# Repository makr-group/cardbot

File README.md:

╔══════════════════════════════════════════════════════════════════╗
    ║                                                                  ║
    ║     ██████╗ █████╗ ██████╗ ██████╗ ██████╗  ██████╗ ████████╗    ║
    ║    ██╔════╝██╔══██╗██╔══██╗██╔══██╗██╔══██╗██╔═══██╗╚══██╔══╝    ║
    ║    ██║     ███████║██████╔╝██║  ██║██████╔╝██║   ██║   ██║       ║
    ║    ██║     ██╔══██║██╔══██╗██║  ██║██╔══██╗██║   ██║   ██║       ║
    ║    ╚██████╗██║  ██║██║  ██║██████╔╝██████╔╝╚██████╔╝   ██║       ║
    ║     ╚═════╝╚═╝  ╚═╝╚═╝  ╚═╝╚═════╝ ╚═════╝  ╚═════╝    ╚═╝       ║
    ║                                                                  ║
    ╚══════════════════════════════════════════════════════════════════╝
    
      █▄▄ █▄█   █▀▄▀█ ▄▀█ █▄▀ █▀█
      █▄█ ░█░   █░▀░█ █▀█ █░█ █▀▄

**Cardbot** is a open source robotics project desinged to bring low costs entry level robots
to students and kids. This project was started by the non-profit Makr Group (aka Makr) to
bring robotics to under served communities in Omaha, Nebraska, USA. With the goal to
kickstart intrest in technology and robotics. The Project is ongoing and slowly growing with 
the capbilites of the robots.

Cardbot is shared under the **Creative Commons Attribution-ShareAlike 4.0 International** license.

## Current Features

- Controller driven Bots with a programmable autonomus mode
- Phone Driven Bots (Broken)
- 3D printer files
- Laser cutter files
- Build Instuctions

## Planned Features

- Full programming instuctions
- Class lesson plans
- Alternative Build Lists

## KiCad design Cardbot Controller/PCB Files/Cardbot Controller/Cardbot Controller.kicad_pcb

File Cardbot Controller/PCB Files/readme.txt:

Files for Controller PCB both Gerber and KiCad.

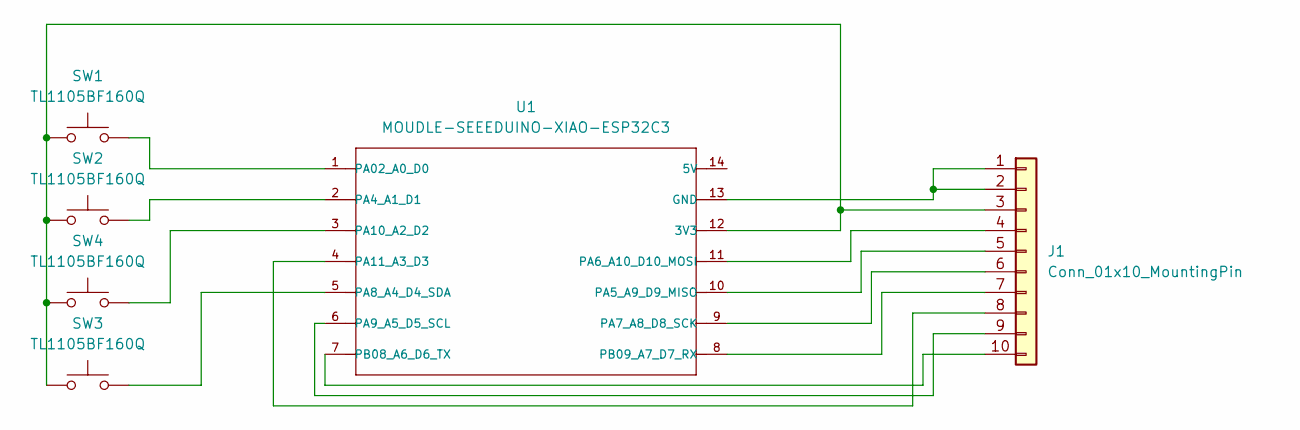
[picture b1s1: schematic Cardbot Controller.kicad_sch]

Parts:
J1: Conn_01x10_MountingPin
SW1, SW2, SW3, SW4: TL1105BF160Q
U1: MOUDLE-SEEEDUINO-XIAO-ESP32C3; MOUDLE14P-SMD-2.54-21X17.8MM

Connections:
unnamed: J1.1, J1.2, U1.13 (GND)
unnamed: J1.3, SW1.1, SW2.1, SW3.1, SW4.1, U1.12 (3V3)
unnamed: J1.4, U1.11 (PA6_A10_D10_MOSI)
unnamed: J1.5, U1.10 (PA5_A9_D9_MISO)
unnamed: J1.6, U1.9 (PA7_A8_D8_SCK)
unnamed: J1.7, U1.8 (PB09_A7_D7_RX)
unnamed: J1.8, U1.4 (PA11_A3_D3)
unnamed: J1.9, U1.6 (PA9_A5_D5_SCL)
unnamed: J1.10, U1.7 (PB08_A6_D6_TX)
unnamed: SW1.2, U1.1 (PA02_A0_D0)
unnamed: SW2.2, U1.2 (PA4_A1_D1)
unnamed: SW3.2, U1.5 (PA8_A4_D4_SDA)
unnamed: SW4.2, U1.3 (PA10_A2_D2)

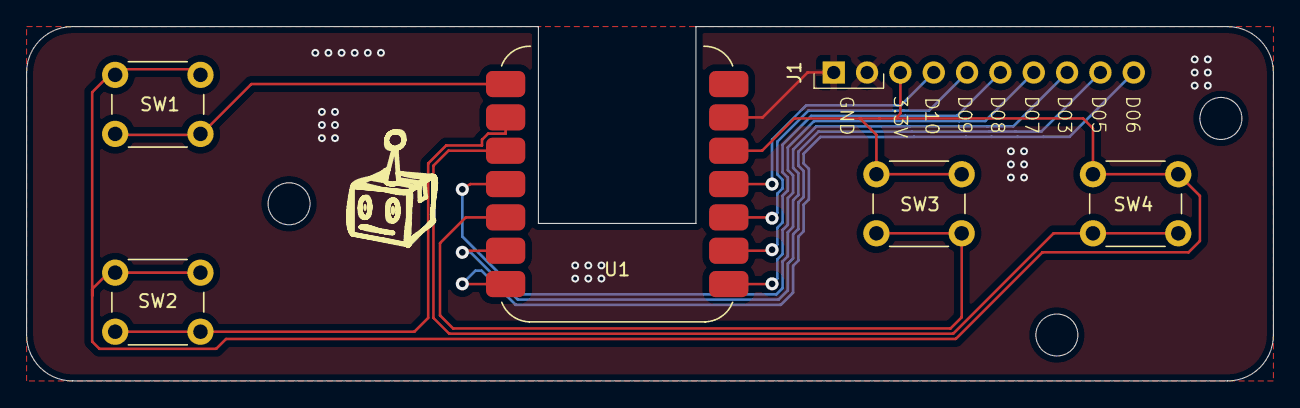
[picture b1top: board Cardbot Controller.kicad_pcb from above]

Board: 2 copper layers, 95.0 x 27.0 mm, 6 parts (0 on the bottom side), 13 nets.

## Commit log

2025-06-24 Added LICENSE.md
    Added Attribution-ShareAlike 4.0 (CC BY-SA) license to cover the project.
2025-06-24 Create cardbot_c_robot_code.ino
    Added Carbot Controller Robot Code
2025-06-24 Delete cardbot_controller_controled directory
    Needed to spell better
2025-06-24 Create cardbot_robot_code_c.cpp
    raw C++ file for controller based cardbot
2025-06-24 Added Arduino code
2025-06-24 Created README.txt for Cardbot Controller
2025-06-24 Create cardbot_controller_code.cpp
    Added raw c++ code for cardbot controller in Arduino format
2025-06-24 Added Arduino code for Cardbot Controller
2025-06-24 Delete cardbot_ controller_controlled/controller/cardbot_controller_code.cpp
    Redundant File
2025-06-24 Delete cardbot_ controller_controlled/robot/cardbot_robot_code_c.cpp
    Redundant File
2025-06-26 Created STEP files for controllers
2025-06-26 Created controller STL files
2025-06-29 Added 3D Printed Parts
2025-06-29 Added Laser Cut Files
2025-06-29 Create laser cut instructions
2025-07-07 Rename Cardbot - Corner Connection.stl to Cardbot - Corner Connector.stl
2025-07-14 Added Cardbot Build Instructions
2025-07-14 Added Part List
2025-07-14 Added Controller Files
2025-07-14 Added Gerber and KiCad Files of PCB
2025-07-14 Added Parts List
2025-07-14 Renamed whole file structure
2025-07-15 Created readme.txt
2025-07-15 Added v1.2 Files
    Updated:
    Updated STL to v1.2
    Updated Instructions
    Updated Parts List
    Added STEP files
2025-07-16 minor update to variable and function names
    updates to variable and function names to be inline with best practices
2025-07-16 updated variable names
    Minor updated to variable names to be inline with standard
2025-07-31 Delete Cardbot Chassis/Cardbot - Tail.stl
    Removed Redundant Files
2025-07-31 Delete Cardbot Chassis/Cardbot - Corner Bracket.stl
    Removed Redundant Files
2025-07-31 Delete Cardbot Chassis/Cardbot - Corner Connector.stl
    Removed Redundant Files
2025-07-31 Delete Cardbot Chassis/Cardbot - Battery Tray.stl
    Removed Redundant Files
2025-07-31 Delete Cardbot Chassis/Cardbot - Motor Plate.stl
    Removed Redundant Files
2025-07-31 Rename Cardbot - Body.svg to Cardbot Body - Frame.svg
    Renamed file to match new naming scheme.
2025-07-31 Update Laser Cut Instuctions.txt
    Added some further instructions.
2025-07-31 Update README.txt
    Wording Update
2025-08-14 Update cardbot_robot_code-controller.ino
    Updated Version Number to v1.1
2025-08-14 Clarified Header Text
    Clarified Header Text
    No longer mentions autonomous mode.
2025-08-17 Update cardbot_controller_code.ino
    Removed needed code line
2025-08-17 Fixed page order of instructions
2025-08-17 Improved part connections
    degreased the needed force to snap together following parts:
    Conner Bracker
    Battery Tray
    Tail
2025-08-19 Removed empty function onDataSent()

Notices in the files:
Cardbot Controller/PCB Files/Cardbot Controller/Cardbot Controller.kicad_pcb:
Cardbot Controller v1.0 - © MAKR Group 2025
